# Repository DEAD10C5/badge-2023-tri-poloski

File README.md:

# взаимоблокировщики - гопник badge - Путин хуйло

## Created by

Будущее подпольной кибер-безопасности

- Concept: Yaya Pancho
- Translations: @muscovitebob
- Puzzle: [Hermit](mailto:hermit@dead10c5.org)
- Hardware: [p0lr](mailto:p0lr@dead10c5.org) [@thedevilsvoice](mailto:thedevilsvoice@dead10c5.org)
- Software: [p0lr](mailto:p0lr@dead10c5.org) [@thedevilsvoice](mailto:thedevilsvoice@dead10c5.org)

)

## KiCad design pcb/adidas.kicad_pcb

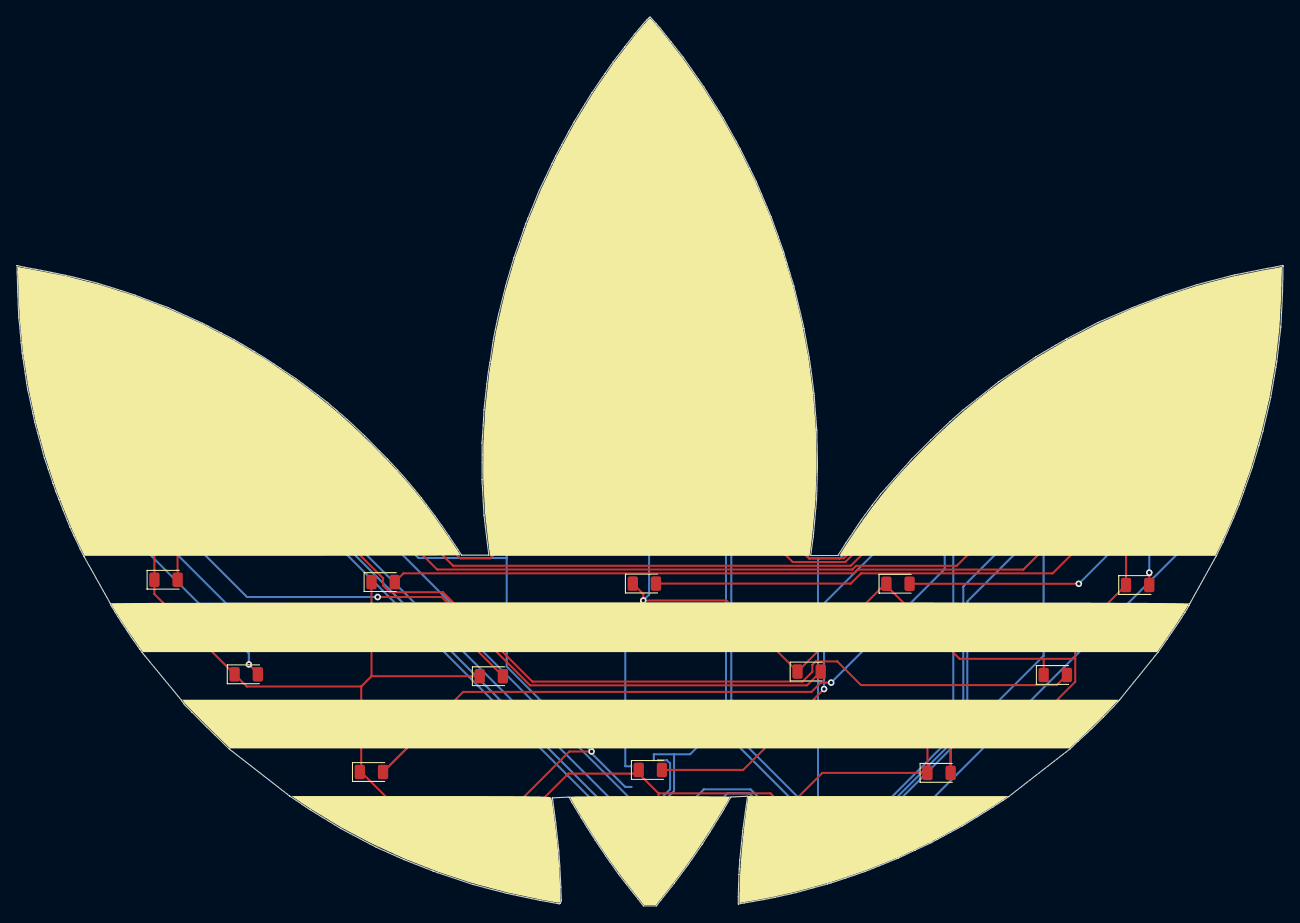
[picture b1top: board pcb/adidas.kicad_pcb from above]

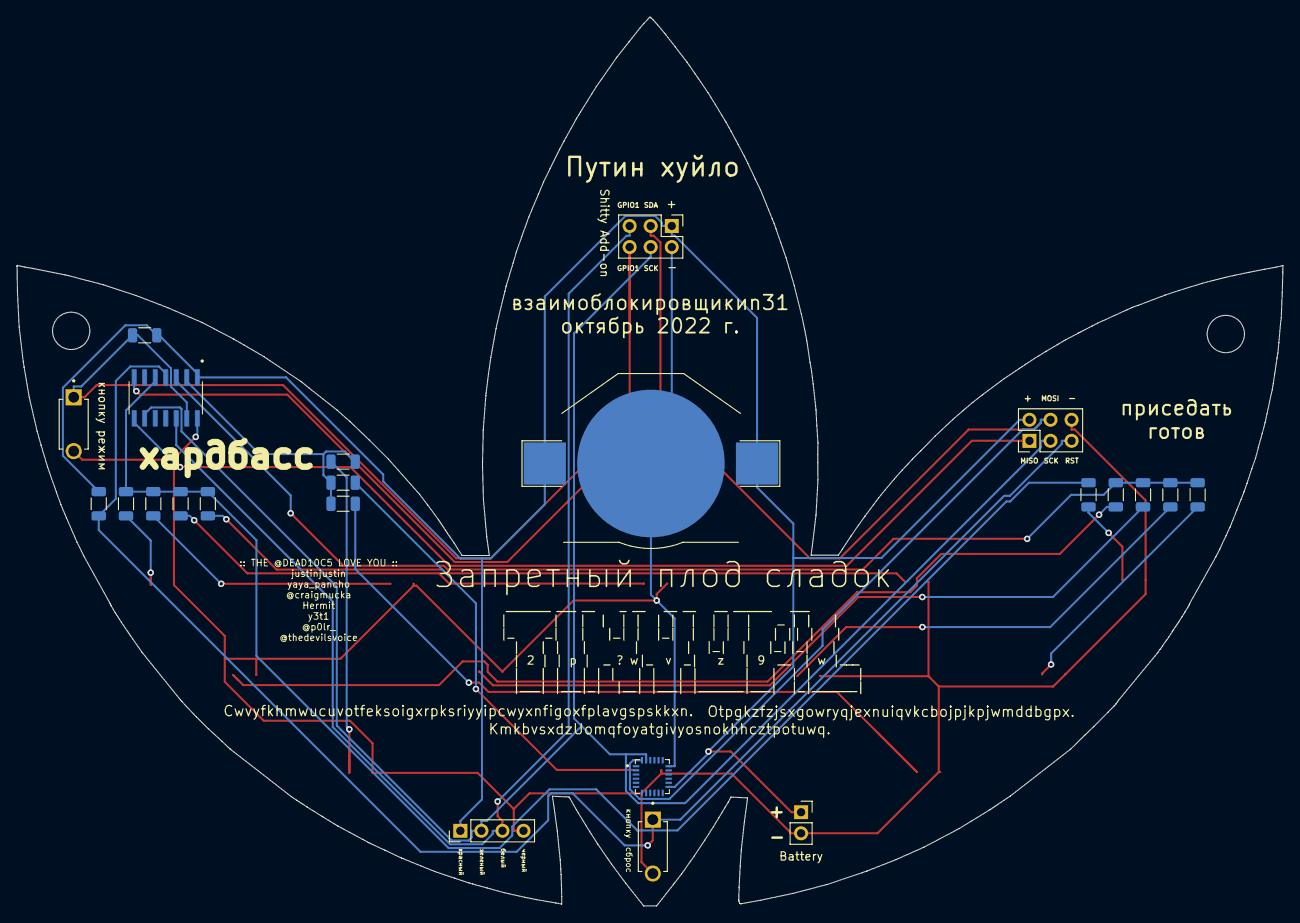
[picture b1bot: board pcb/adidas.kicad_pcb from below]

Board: 2 copper layers, 152.7 x 107.2 mm, 38 parts (23 on the bottom side), 23 nets.

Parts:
BT1: монетная батарейка; BatteryHolder_Keystone_3002_1x2032
D1, D2, D3, D4, D5, D6, D7, D8, D9, D10, D11, D12: SM1206NHC-IL; LED_1206_3216Metric
J1: ISP Header; PinHeader_2x03_P2.54mm_Vertical
J2: Shitty Add-on; PinHeader_2x03_P2.54mm_Vertical
J3: Conn_01x04_Pin; PinHeader_1x04_P2.54mm_Vertical
J4: Battery; PinSocket_1x02_P2.54mm_Vertical
R1, R2, R3, R4, R5, R6, R7, R8, R9, R10, R11, R12: 220Ω; R_1206_3216Metric
R13: 10kΩ; R_1206_3216Metric
R14: 470Ω; R_1206_3216Metric
S1, S2: TL1107BF180WQ; SW_TL1107BF130WQ
U1: MPU-6050; QFN50P400X400X95-24N
U2: ATTINY841-SSU; SOIC127P599X175-14N
hole1, hole2: MountingHole_4.5mm
silkscreen: LOGO; Adidas_Logo

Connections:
/2(LED Bottom Row): R1.1, R2.1, R3.1, U2.2 (PB0)
/3(LED Mid Row): R4.1, R5.1, R6.1, R7.1, U2.3 (PB1)
/4(RST): J1.5, R13.2, S1.1, U2.4 (PB3)
/5(LED Top Row): R8.1, R9.1, R10.1, R11.1, R12.1, U2.5 (PB2)
/7(SDA/MOSI): J1.4, J2.3, U1.24 (SDA), U2.7 (PA6)
/8(MISO): J1.1, U2.8 (PA5)
/9(SCK): J1.3, J2.4, J3.2, U1.23 (SCL), U2.9 (PA4)
/12(SAO2): J2.5, J3.3, U2.12 (PA1)
/13(SAO1): J2.6, R14.1, S2.1, U2.13 (PA0)
GND: BT1.2 (-), D1.1, D2.1, D3.1, D4.1, D5.1, D6.1, D7.1, D8.1, D9.1, D10.1, D11.1, D12.1, J1.6, J2.2, J3.4, J4.2, S1.2, S2.2, U1.18 (GND), U2.14 (GND)
unnamed: D1.2, R1.2
unnamed: D2.2, R2.2
unnamed: D3.2, R3.2
unnamed: D4.2, R4.2
unnamed: D5.2, R5.2
unnamed: D6.2, R6.2
unnamed: D7.2, R7.2
unnamed: D8.2, R8.2
unnamed: D9.2, R9.2
unnamed: D10.2, R10.2
unnamed: D11.2, R11.2
unnamed: D12.2, R12.2
VDD: BT1.1 (+), J1.2, J2.1, J3.1, J4.1, R13.1, R14.2, U1.13 (VDD), U2.1 (VCC)

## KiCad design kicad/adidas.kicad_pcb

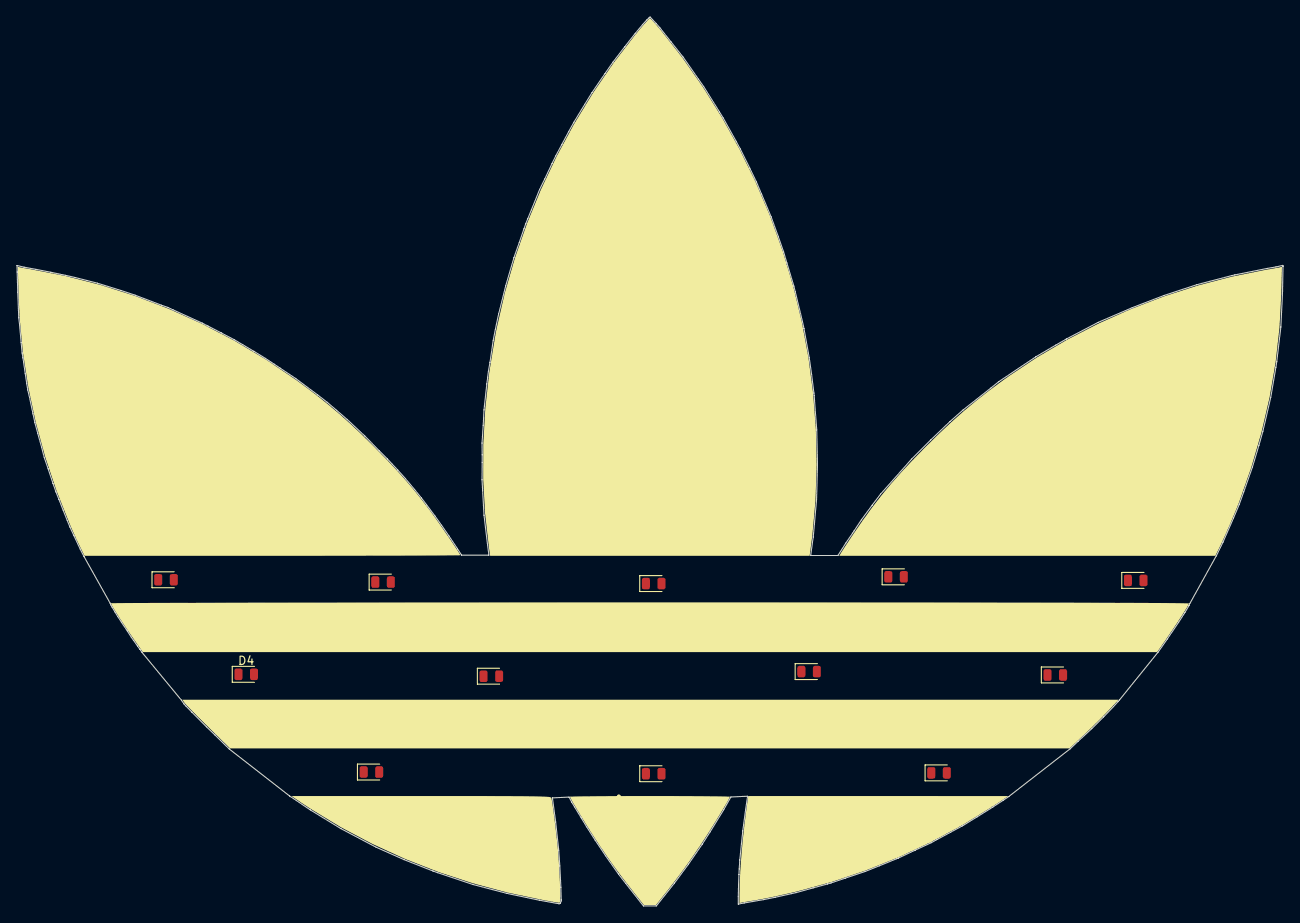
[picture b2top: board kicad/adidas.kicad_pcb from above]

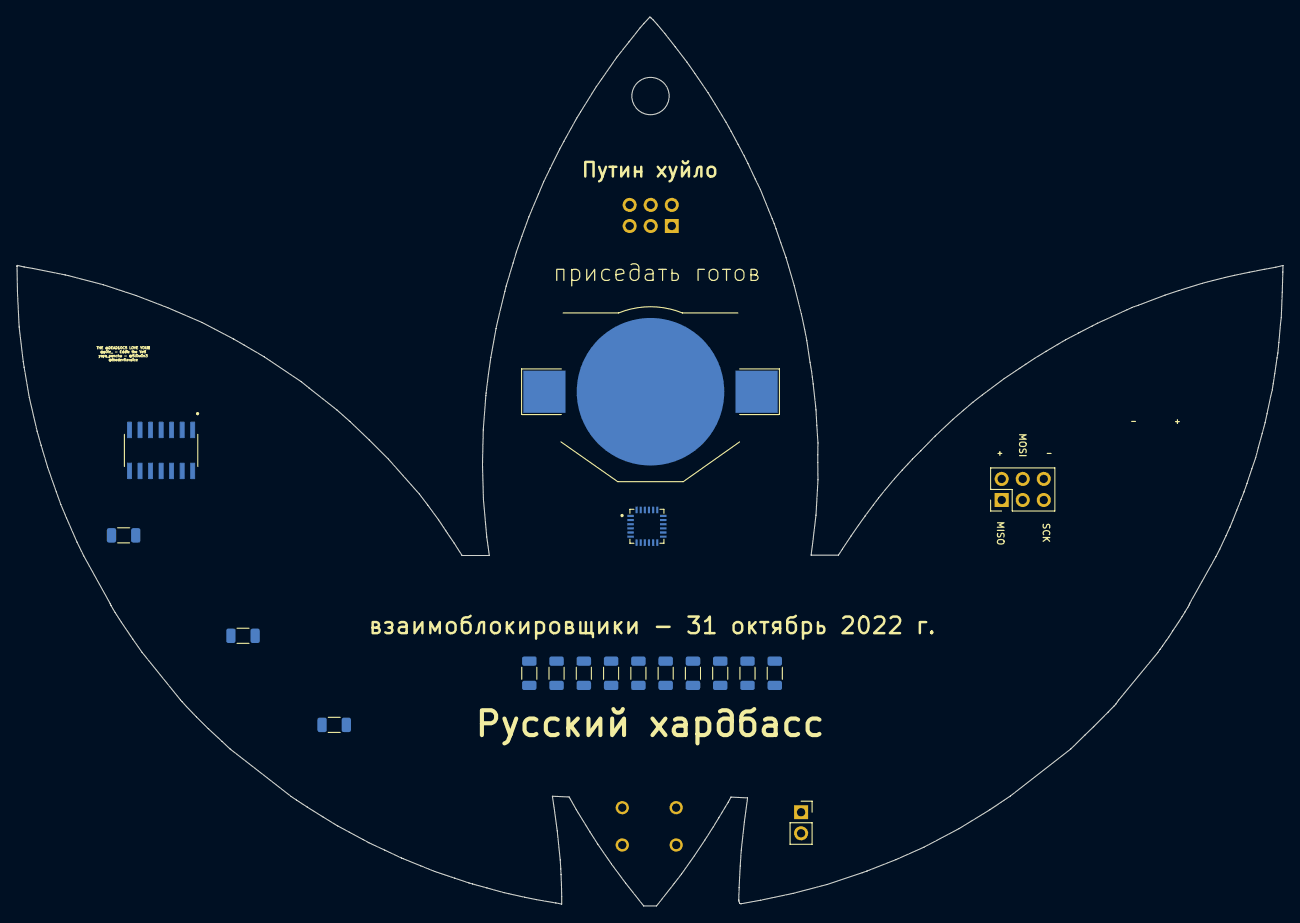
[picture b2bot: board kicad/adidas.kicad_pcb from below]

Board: 2 copper layers, 152.7 x 107.2 mm, 33 parts (18 on the bottom side), 23 nets, no tracks yet.

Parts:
BT1: Battery_Cell; BatteryHolder_Keystone_3002_1x2032
D1, D2, D3, D4, D5, D6, D7, D8, D9, D10, D12: LHN974; LED_0805_2012Metric
D11: LED_0805_2012Metric
J1: ISP Header; PinHeader_2x03_P2.54mm_Vertical
J2: Shitty Add-on; PinHeader_2x03_P2.54mm_Vertical
J4: Battery; PinSocket_1x02_P2.54mm_Vertical
R1, R2, R3, R4, R5, R6, R7, R8, R9, R10, R11, R12: 220Ω; R_1206_3216Metric
R13: 10kΩ; R_1206_3216Metric
S1: B3F-1000; SW_B3F-1000
U1: MPU-6050; QFN50P400X400X95-24N
U2: ATTINY841-SSU; SOIC127P599X175-14N
silkscreen: LOGO; Adidas_Logo

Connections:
/2(LED Bottom Row): R1.1, R4.1, R5.1, U2.2 (PB0)
/3(LED Mid Row): R2.2, R6.2, R7.2, R8.2, U2.3 (PB1)
/4(RST): J1.5, R13.2, S1.3, U2.4 (PB3)
/5(LED Top Row): R3.1, R9.1, R10.1, R11.1, R12.1, U2.5 (PB2)
/7(SDA): J1.4, J2.3, U1.24 (SDA), U2.7 (PA6)
/9(SCL): J1.3, J2.4, U1.23 (SCL), U2.9 (PA4)
/12(SAO2): J2.5, U2.12 (PA1)
/13(SAO1): J2.6, U2.13 (PA0)
GND: BT1.2 (-), D1.1, D2.1, D3.1, D4.1, D5.1, D6.1, D7.1, D8.1, D9.1, D10.1, D11.1, D12.1, J1.6, J2.2, J4.2, S1.1, U1.18 (GND), U2.14 (GND)
unnamed: D1.2, R1.2
unnamed: D2.2, R4.2
unnamed: D3.2, R5.2
unnamed: D4.2, R2.1
unnamed: D5.2, R6.1
unnamed: D6.2, R7.1
unnamed: D7.2, R8.1
unnamed: D8.2, R3.2
unnamed: D9.2, R9.2
unnamed: D10.2, R10.2
unnamed: D11.2, R11.2
unnamed: D12.2, R12.2
unnamed: J1.1, U2.8 (PA5)
VCC: J1.2, J4.1, R13.1, U1.13 (VDD), U2.1 (VCC)

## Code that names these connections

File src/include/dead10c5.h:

/*!
   @file dead10c5.h
    ____  _____      _    ____    _  ___     ____ ____
   |  _ \| ____|_   / \  |  _ \ _/ |/ _ \ _ / ___| ___|
   | | | |  _| (_) / _ \ | | | (_) | | | (_) |   |___ \
   | |_| | |___ _ / ___ \| |_| |_| | |_| |_| |___ ___) |
   |____/|_____(_)_/   \_\____/(_)_|\___/(_)\____|____/


   Author : @theDevilsVoice https://twitter.com/dead10c5
   Date   : April 3, 2023
   Version: 0.2
*/
#ifndef DEAD10C5_H
#define DEAD10C5

#define VERSION "v0.2 - 03 April 2023 - гопник badge - Путин хуйло"

#include <Arduino.h> // default library for Arduino
// #include <Wire.h>           // used for the I2C communication
#include <SoftwareSerial.h> // used for serial output on the badge
// #include <TinyI2CMaster.h> // this one says it is not compatible with 841
#include "TinyWireM.h"

const uint8_t BOTTOM_ROW = PA0; // PB0 on pin2
const uint8_t MIDDLE_ROW = PA1; // PB1 on pin3
const uint8_t TOP_ROW = PB2;    // PB2 on pin5

// MPU6050 https://github.com/nadavmatalon/TinyWireM/tree/master/examples/TinyWireM_example/ATtiny841_Master
const byte SLAVE_ADDR = 100;
unsigned long timeNow;
boolean slavePresent = false;
byte data = 0;

#define SDA_PORT PORTA
#define SDA_PIN PORTA0

#define SCL_PORT PORTA
#define SCL_PIN PORTA5

#endif

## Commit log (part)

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2022-08-26 Add .whitesource configuration file
2022-08-26 added bmp logo
2022-08-26 initial art
2022-08-26 moving items to appropriate directories;
2022-08-26 v0.1
2022-08-27 admin pieces
2022-09-02 resized art and created outline
2022-09-02 updates (#3)
2022-09-02 add 6050 footprint
2022-09-02 add mpu6050 part (#4)
    * add mpu6050 part
    * add 6050 footprint
2022-09-02 add arduino structure
2022-09-03 testing the IDE
2022-09-03 add arduino structure (#5)
    * add arduino structure
    * testing the IDE
    * testing the IDE
2022-09-04 add a microcontroller
2022-09-04 test ISP header
2022-09-04 test LED placement
2022-09-04 place chips in schematic
2022-09-05 update schematic
2022-09-06 place chips in schematic (#7)
    * place chips in schematic
    * update schematic
    * update schematic
2022-09-06 add SAO header and place LEDs
2022-09-07 add SAO header and place LEDs (#8)
2022-09-13 update IDE setup steps
2022-09-18 update IDE setup steps (#9)
2022-09-18 run freeroute on the PCB
2022-09-18 move components (#10)
    * move components
    * run freeroute on the PCB
    * run freeroute on the PCB
    * move components
2022-09-25 Add renovate.json
2022-10-04 Add renovate.json (#11)
2022-10-04 run DRC
2022-10-04 run DRC (#13)
    * run DRC
    * run DRC
2022-10-14 Путин хуйло
2022-10-15 remove zip file
2022-10-15 add BOM for parts ordering
2022-10-15 Путин хуйло (#14)
    * Путин хуйло
    * remove zip file
    * update back silkscreen
    * update back silkscreen
    * add BOM for parts ordering
2022-10-15 fix filename typo
2022-10-15 fix filename typo (#15)
2022-10-26 update bom
2022-10-26 move resistor to back and update routing
2022-10-26 update bom (#16)
    * update bom
    * move resistor to back and update routing
2023-02-18 add some file
2023-02-18 add cloudbot
2023-02-18 add cloudbot (#18)
2023-02-18 update for KiCAD 7
2023-02-18 checkpoint (#17)
    * checkpoint
    * add some file
    * update for KiCAD 7
2023-02-18 shrink the text on the credits
2023-02-18 testing new kicad with kibot
2023-02-18 testing container image
2023-02-18 cleanup files
2023-02-18 Cleanup for production (#19)
    * checkpoint
    * add some file
    * update for KiCAD 7
    * shrink the text on the credits
    * testing new kicad with kibot
    * testing container image
2023-02-18 manage these jank ass libraries
2023-02-18 manage these jank ass libraries (#21)
    * manage these jank ass libraries
    * manage these jank ass libraries
    * manage these jank ass libraries
2023-02-18 update kibot files
2023-02-18 when is this going to work
2023-02-18 generate gerbers
2023-02-18 remove extra action
2023-02-18 update kibot files (#22)
    * update kibot files
    * when is this going to work
    * generate gerbers
    * generate the BOM
    * remove extra action
2023-02-19 code for the board
2023-02-19 generate 3d front and back images
2023-02-22 changes after feedback from PCBway
2023-02-22 make more updates after PCBway feedback
2023-02-22 code for the board (#23)
    * code for the board
    * generate 3d front and back images
    * changes after feedback from PCBway
    * make more updates after PCBway feedback
2023-02-22 updates to board
2023-02-22 board updates
2023-02-22 update action
2023-02-22 add markdown action
2023-02-22 update kibot action
2023-02-22 updates to board (#24)
    * updates to board
    * updates to board
    * tune action
    * board updates
    * update action
    * add markdown action
2023-02-22 refactor
2023-02-22 cleanup for v0.2
2023-02-22 RUN DRC v0.2 (#25)
    * refactor
    * RUN DRC
    * cleanup for v0.2
    * final v0.2
2023-02-22 Update actions/upload-artifact action to v3.1.2 (#26)
2023-02-23 make some changes from PCBway feedback v0.3
2023-02-23 tune actions
2023-02-23 add mouser and digikey part numbers
2023-02-23 run ERC checks
2023-02-24 make some changes from PCBway feedback v0.3 (#27)
    * make some changes from PCBway feedback v0.3
    * tune actions
    * add mouser and digikey part numbers
    * run ERC checks
    * run ERC checks
2023-02-24 kibot testing
2023-02-24 update the battery clip in the BOM
2023-02-24 BOM updates (#29)
    * update schematic
    * update schematic
    * update the battery clip in the BOM
2023-02-24 more BOM updates
2023-02-25 more BOM updates (#30)
2023-02-25 update graphics
2023-02-27 change out the LED component
2023-02-27 update graphics (#31)
    * update graphics
    * change out the LED component
2023-04-01 testing accelerometer
2023-04-01 add BF3-1000 switch datasheet
2023-04-01 add some assembly notes
2023-04-01 add some LED code
2023-04-01 update programming instructions
2023-04-03 burnt bootloader on baords
2023-04-03 testing board flash
2023-04-03 testing bootloader burn (#33)
    * testing accelerometer
    * add BF3-1000 switch datasheet
    * add some assembly notes
    * add some LED code
    * update programming instructions
    * update programming instructions
2023-04-03 replace missing serial start
2023-04-03 cleanup
2023-04-03 testing LED set (#34)
    * testing LED set
    * replace missing serial start
    * cleanup
2023-04-03 testing hardware
2023-04-03 Test platformio build
2023-04-03 Test platformio build (#35)
    * Test platformio build
    * Test platformio build
    * Test platformio build
    * Test platformio build
    * Test platformio build
2023-04-03 Test code cleanup
2023-04-03 reduce the skecth footprint
2023-04-03 Hardware testing (#36)
    * testing hardware
    * Test code cleanup
    * enable the accelerometer code
    * enable the accelerometer code
    * enable the accelerometer code
    * reduce the skecth footprint
2023-04-04 update documentation
2023-04-04 replace B3F-100 switch
2023-04-04 lint issue
2023-04-04 update switches, re-add the lanyard hole
2023-04-04 update documentation (#39)
    * update documentation
    * update documentation
    * update documentation
    * lint issue
2023-04-04 replace B3F-100 switch (#40)
    * replace B3F-100 switch
    * update switches, re-add the lanyard hole
2023-04-04 remove all traces, move chip and battery holder
2023-04-05 testing mpu6050
2023-04-05 add tiny i2c
2023-04-05 fix dep5
2023-04-05 add TInyWireM
2023-04-05 update C++ build (#41)
    * update C++ build
    * remove all traces, move chip and battery holder
    * remove all traces, move chip and battery holder
2023-04-05 test platformio
2023-04-05 add i2c test code
2023-04-05 disable platformio for now
2023-04-05 testing mpu6050 (#42)
    * testing mpu6050
    * add tiny i2c
    * fix dep5
    * add TInyWireM
    * test platformio
    * move header file
2023-04-05 capture schematic
2023-04-05 update 3d captures
2023-04-06 test sketch written to boards
2023-04-06 capture schematic (#43)
    * capture schematic
    * update 3d captures
    * test sketch written to boards
2023-04-14 split design to new folder
2023-05-11 redo routing on PCB
2023-05-11 refactor a bit
2023-05-11 more moounting holes
2023-05-11 tune up reuse
2023-05-11 update names
2023-05-11 random checkpoint (#44)
    * random checkpoint
    * redo routing on PCB
    * refactor a bit
    * more moounting holes
    * tune up reuse
    * tune up reuse
2023-05-11 fix refactor
2023-05-13 work on hardware test code
2023-05-13 testing mpu6050 hardware
2023-05-13 work on hardware test code (#46)
    * work on hardware test code
    * testing mpu6050 hardware
2023-05-14 documentation updates
2023-05-14 documentation updates (#48)
    * documentation updates
    * documentation updates
    * documentation updates
2023-05-14 fix battery clip
2023-05-14 fix reversed battery clip leads (#49)
    * documentation updates
    * documentation updates
    * documentation updates
    * fix battery clip
2023-05-15 hardware testing
2023-05-15 add some docs on how the new test code is meant to work
2023-05-15 add docs for flashing the boards
2023-05-16 add test pin breakouts
2023-05-17 more testing
2023-05-17 checkpoint some test code
2023-05-18 add serial port
2023-05-18 testing pins
2023-05-18 hardware testing (#50)
    * hardware testing
    * hardware testing
    * new hardware test with wire library
    * add some docs on how the new test code is meant to work
    * add docs for flashing the boards
    * add test pin breakouts
2023-05-18 Add some notes on opening the project
2023-05-18 Add some notes on building the project
2023-05-18 Add some notes on adding the TinyMPU6050 library
2023-05-18 Remove trailing space after line wrap
2023-05-23 Doc changes while setting up on MacOS (#52)
    * Tweaking doc for MacOS
    * Tweaking doc for MacOS
    * Add some notes on opening the project
    * Add some notes on building the project
    * Add some notes on adding the TinyMPU6050 library
    * Remove trailing space after line wrap
2023-05-24 reduce the clutter
2023-05-24 more cleanup of the docs
2023-05-24 clean up docs
2023-05-24 clean up the docs (#53)
    * reduce the clutter
    * more cleanup of the docs
    * clean up markdown
    * clean up docs
2023-05-24 clean up serial docs
2023-05-24 hardware test working
2023-05-24 clean up serial docs (#54)
    * clean up serial docs
    * hardware test working
    * hardware test working
2023-05-29 updates to the back of the board
2023-05-29 updates to the back of board
2023-05-30 update puzzle
2023-05-31 testing puzzle placement
2023-05-31 update back of board
2023-05-31 work on puzzle
2023-05-31 puzzle updates
2023-05-31 dep5 update
2023-05-31 row3
2023-05-31 testing
2023-06-01 fix script to update reference designators on puzzle footprints
2023-06-01 routing
2023-06-01 fix script to update reference designators on puzzle footprints (#56)
    * fix script to update reference designators on puzzle footprints
    * routing
2023-06-01 flip the battery clip
2023-06-01 update BOM and generate gerbers
2023-06-01 flip the battery clip (#57)
    * flip the battery clip
    * update BOM and generate gerbers
2023-06-08 work on the puzzle tool
2023-06-12 where are these gerbers coming from
2023-06-12 update artwork
2023-06-12 final snapshot
2023-06-12 final final final
2023-06-12 work on the puzzle tool (#58)
2023-06-12 puzzle graphic update (#60)
    * update artwork
    * final snapshot
    * final final final
2023-07-16 update images
2023-07-16 update images (#62)
    * update images
    * update images
    * update images
2023-07-19 fix the pin naming in the schematic
2023-07-19 update the silkscreen on the back of the board for the pin name changes
2023-07-21 Update fsfe/reuse-action action to v1.3.0 (#66)
2023-07-21 Update fsfe/reuse-action action to v2
2023-07-21 Update fsfe/reuse-action action to v2 (#67)
2023-07-21 light patterns (#63)
2023-07-21 fix the pin naming in the schematic (#65)
    * fix the pin naming in the schematic
    * update the silkscreen on the back of the board for the pin name changes
2023-08-03 what is this crap
2023-08-03 clean up the code
2023-08-03 updates (#68)
    * what is this crap
    * add blink light patterns
    * clean up the code
2023-08-03 work on finale code
2023-08-03 review current code
2023-08-03 checkpoint during testing
2023-08-03 final code, serial test
2023-08-04 testing some more
2023-08-04 fix markdown lint
2023-08-04 test badge code and hardware (#69)
    * what is this crap
    * work on finale code
    * clean up the code
    * review current code
    * checkpoint during testing
    * final code, serial test
2023-08-04 what is this crap (#70)
2023-08-05 doing some gyroscope testing
2023-08-21 updates to code
2023-08-24 updates to PRL
2023-09-04 Update actions/checkout action to v4
2023-10-03 code updates (#71)
    * doing some gyroscope testing
    * updates to code
    * updates to PRL
2023-10-03 add images
2023-10-03 add headset meme
2023-10-03 add images (#73)
    * add images
    * add headset meme
2024-05-05 checkpointing
2024-05-24 latest kicad
2024-05-24 checkpointing (#74)
    * checkpointing
    * latest kicad
2024-05-24 Update actions/setup-python action to v5
2024-05-24 Update actions/setup-python action to v5 (#76)
2024-05-24 move image file
2024-05-24 update README.md (#77)
    * update README.md
    * update README.md
    * move image file
2024-05-24 Update fsfe/reuse-action action to v3
2024-05-24 Update google-github-actions/auth action to v2
2024-05-25 Update google-github-actions/setup-gcloud action to v2
2024-05-27 Update fsfe/reuse-action action to v3 (#79)
